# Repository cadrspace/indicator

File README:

# -*- mode: org; -*-

"It's an indicator.  It understands everything, but doesn't speak.  It
only changes colour." -- [[https://en.wikipedia.org/wiki/The_Mystery_of_the_Third_Planet]["The Mystery of the Third Planet"]]

* Requirements
  - [[https://www.gnu.org/software/guile/][GNU Guile]] 2.0+
  - [[https://www.gnu.org/software/guile-rpc/][GNU Guile-RPC]]

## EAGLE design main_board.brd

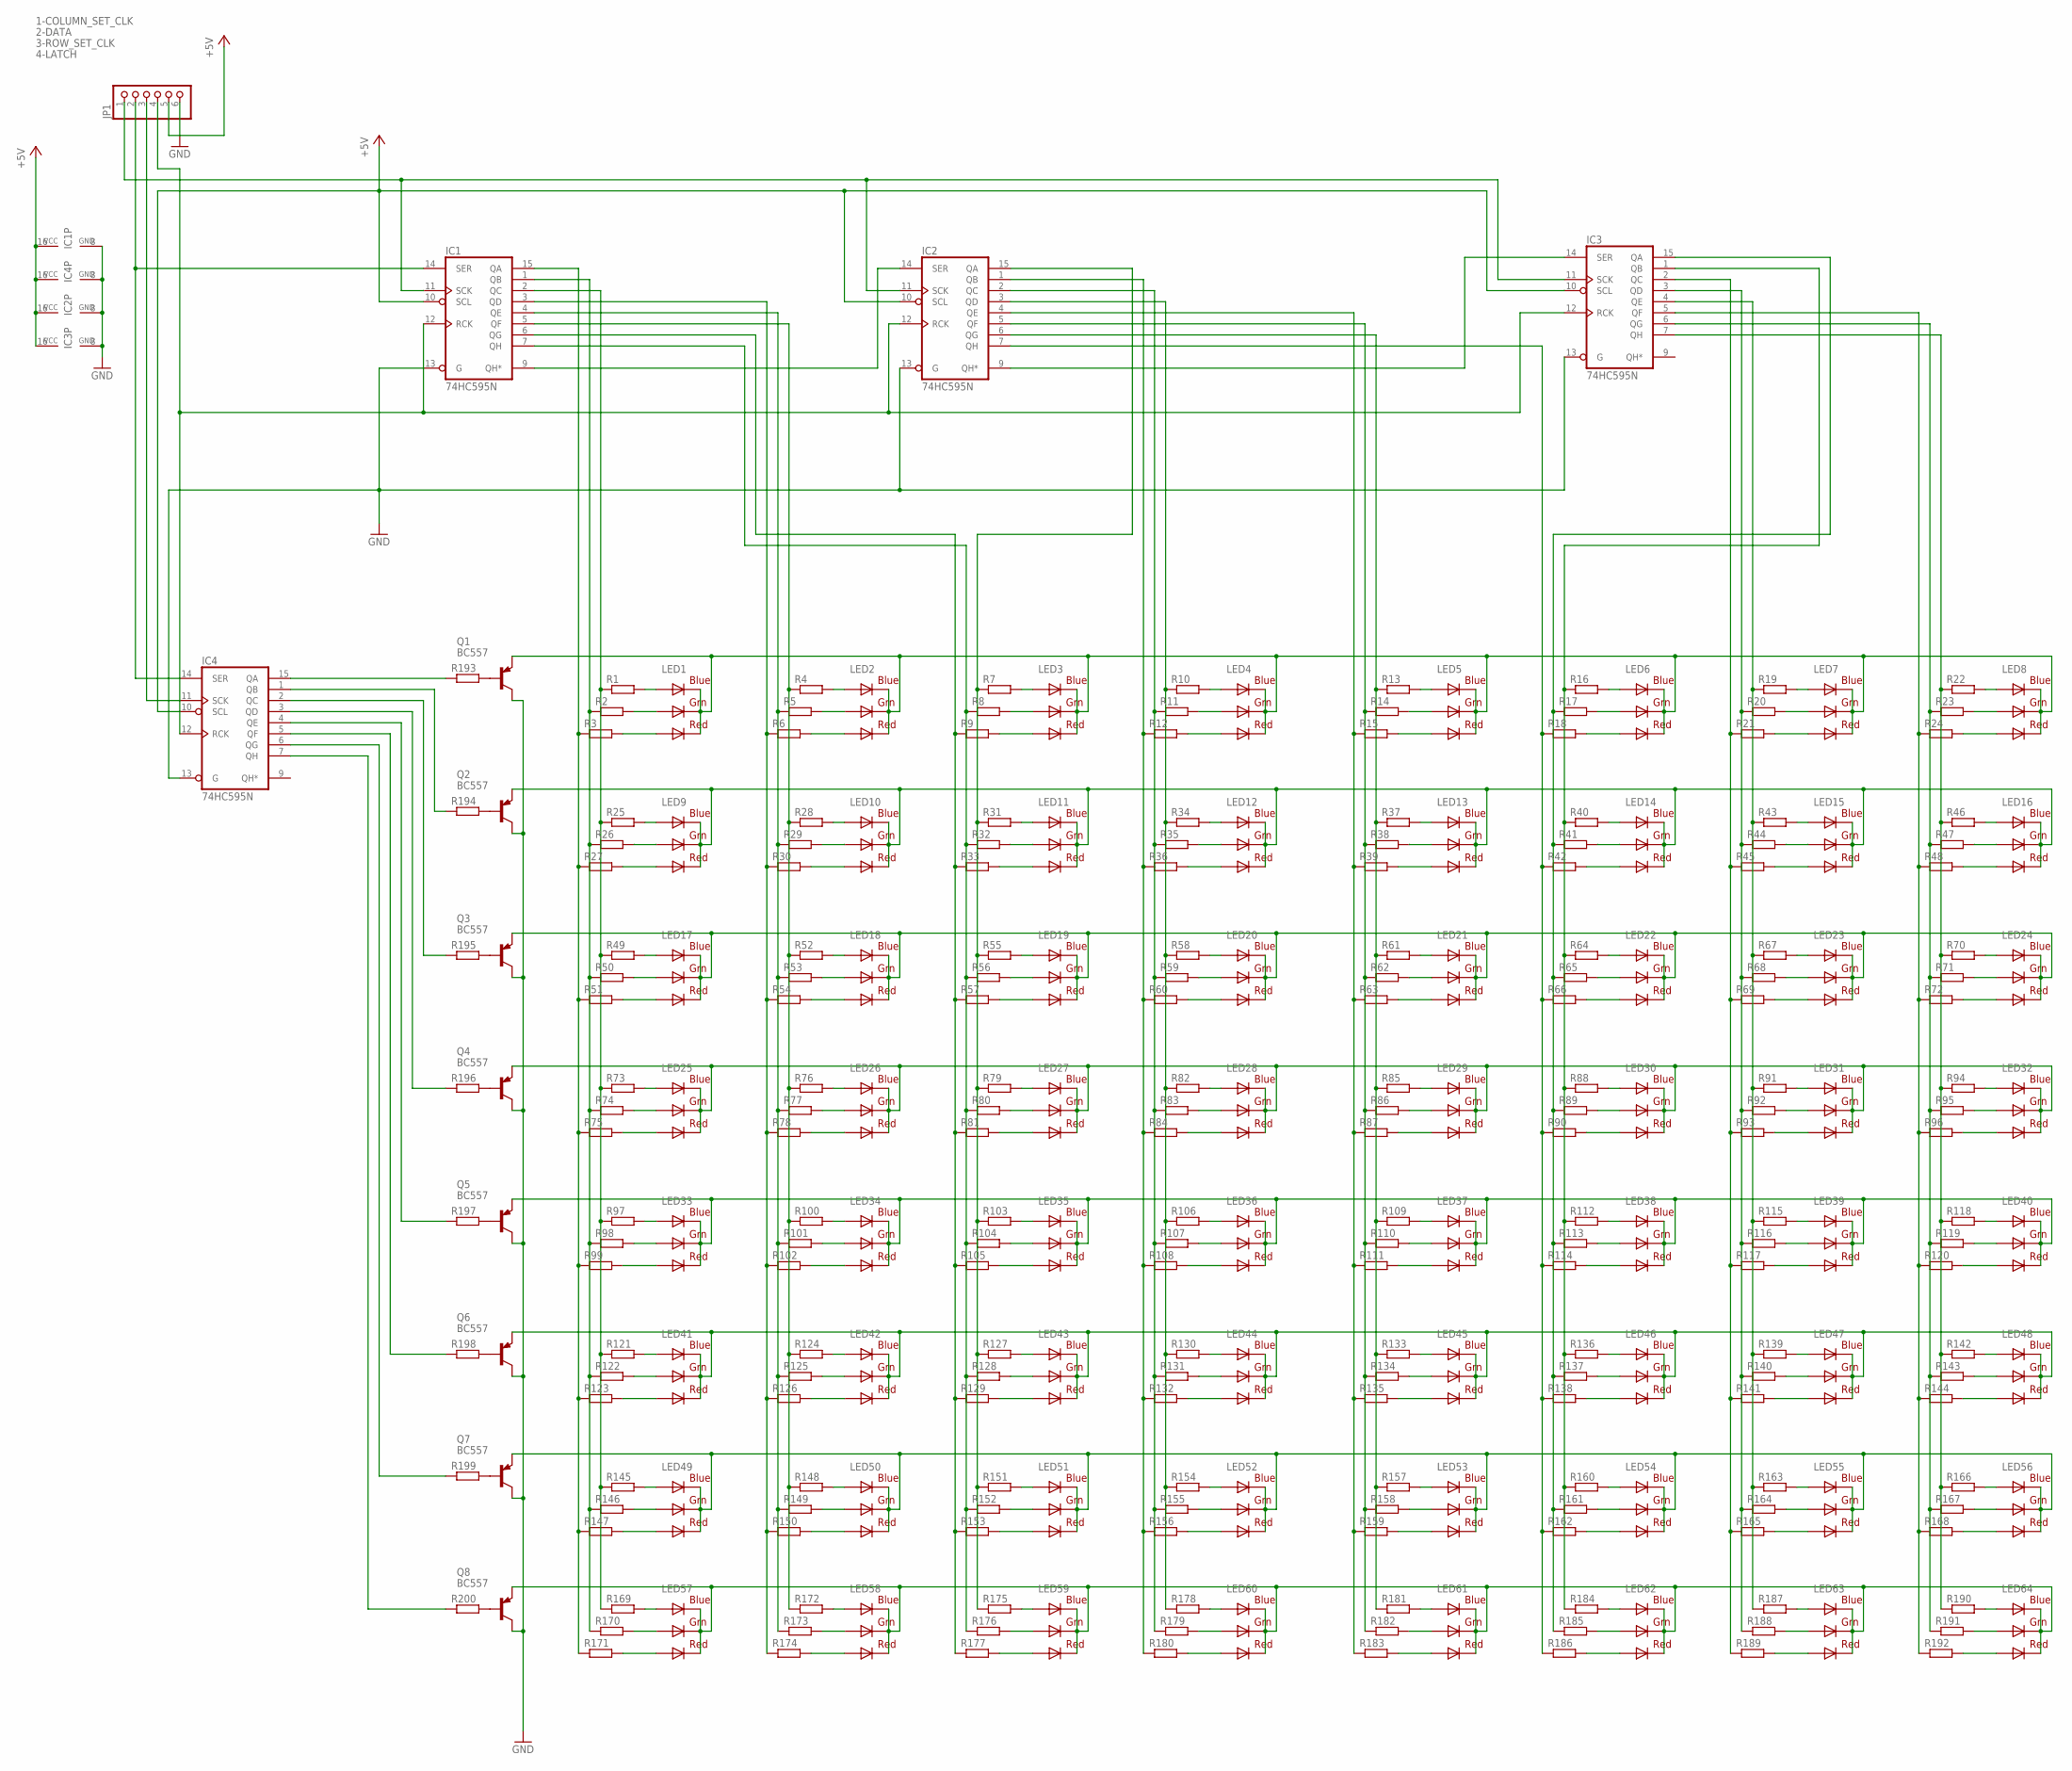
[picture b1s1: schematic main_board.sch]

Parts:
IC1, IC2, IC3, IC4: 74HC595N; DIL16
JP1: PINHD-1X6; 1X06
LED1, LED2, LED3, LED4, LED5, LED6, LED7, LED8, LED9, LED10, LED11, LED12, LED13, LED14, LED15, LED16, LED17, LED18, LED19, LED20, LED21, LED22, LED23, LED24, LED25, LED26, LED27, LED28, LED29, LED30, LED31, LED32, LED33, LED34, LED35, LED36, LED37, LED38, LED39, LED40, LED41, LED42, LED43, LED44, LED45, LED46, LED47, LED48, LED49, LED50, LED51, LED52, LED53, LED54, LED55, LED56, LED57, LED58, LED59, LED60, LED61, LED62, LED63, LED64: RGBLED5050
Q1, Q2, Q3, Q4, Q5, Q6, Q7, Q8: BC557; TO92
R1, R2, R3, R4, R5, R6, R7, R8, R9, R10, R11, R12, R13, R14, R15, R16, R17, R18, R19, R20, R21, R22, R23, R24, R25, R26, R27, R28, R29, R30, R31, R32, R33, R34, R35, R36, R37, R38, R39, R40, R41, R42, R43, R44, R45, R46, R47, R48, R49, R50, R51, R52, R53, R54, R55, R56, R57, R58, R59, R60, R61, R62, R63, R64, R65, R66, R67, R68, R69, R70, R71, R72, R73, R74, R75, R76, R77, R78, R79, R80, R81, R82, R83, R84, R85, R86, R87, R88, R89, R90, R91, R92, R93, R94, R95, R96, R97, R98, R99, R100, R101, R102, R103, R104, R105, R106, R107, R108, R109, R110, R111, R112, R113, R114, R115, R116, R117, R118, R119, R120, R121, R122, R123, R124, R125, R126, R127, R128, R129, R130, R131, R132, R133, R134, R135, R136, R137, R138, R139, R140, R141, R142, R143, R144, R145, R146, R147, R148, R149, R150, R151, R152, R153, R154, R155, R156, R157, R158, R159, R160, R161, R162, R163, R164, R165, R166, R167, R168, R169, R170, R171, R172, R173, R174, R175, R176, R177, R178, R179, R180, R181, R182, R183, R184, R185, R186, R187, R188, R189, R190, R191, R192, R193, R194, R195, R196, R197, R198, R199, R200: R-EU_R0805; R0805

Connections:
1-COLUMN_SET_CLK: IC1.11 (SCK), IC2.11 (SCK), IC3.11 (SCK), JP1.1
2-DATA: IC1.14 (SER), IC4.14 (SER), JP1.2
3-ROW_SET_CLK: IC4.11 (SCK), JP1.3
4-LATCH: IC1.12 (RCK), IC2.12 (RCK), IC3.12 (RCK), IC4.12 (RCK), JP1.4
+5V: IC1.10 (SCL), IC1.16 (VCC), IC2.10 (SCL), IC2.16 (VCC), IC3.10 (SCL), IC3.16 (VCC), IC4.10 (SCL), IC4.16 (VCC), JP1.5
GND: IC1.8 (GND), IC1.13 (G), IC2.8 (GND), IC2.13 (G), IC3.8 (GND), IC3.13 (G), IC4.8 (GND), IC4.13 (G), JP1.6, Q1.3 (C), Q2.3 (C), Q3.3 (C), Q4.3 (C), Q5.3 (C), Q6.3 (C), Q7.3 (C), Q8.3 (C)
unnamed: Q8.2 (B), R200.2
unnamed: LED57.3 (BLUE_A), R169.2
unnamed: LED57.1 (GREEN_A), R170.2
unnamed: LED57.2 (RED_A), R171.2
unnamed: LED58.3 (BLUE_A), R172.2
unnamed: LED58.1 (GREEN_A), R173.2
unnamed: IC2.2 (QC), R11.1, R35.1, R59.1, R83.1, R107.1, R131.1, R155.1, R179.1
unnamed: LED58.2 (RED_A), R174.2
unnamed: LED59.1 (GREEN_A), R176.2
unnamed: LED59.2 (RED_A), R177.2
unnamed: LED59.3 (BLUE_A), R175.2
unnamed: LED1.3 (BLUE_A), R1.2
unnamed: LED1.1 (GREEN_A), R2.2
unnamed: LED1.2 (RED_A), R3.2
unnamed: LED2.3 (BLUE_A), R4.2
unnamed: LED2.1 (GREEN_A), R5.2
unnamed: LED2.2 (RED_A), R6.2
unnamed: LED3.3 (BLUE_A), R7.2
unnamed: LED3.1 (GREEN_A), R8.2
unnamed: LED3.2 (RED_A), R9.2
unnamed: LED4.3 (BLUE_A), R10.2
unnamed: LED4.1 (GREEN_A), R11.2
unnamed: LED4.2 (RED_A), R12.2
unnamed: LED5.3 (BLUE_A), R13.2
unnamed: LED5.1 (GREEN_A), R14.2
unnamed: LED5.2 (RED_A), R15.2
unnamed: LED7.3 (BLUE_A), R19.2
unnamed: LED7.1 (GREEN_A), R20.2
unnamed: LED7.2 (RED_A), R21.2
unnamed: LED8.3 (BLUE_A), R22.2
unnamed: LED8.1 (GREEN_A), R23.2
unnamed: LED8.2 (RED_A), R24.2
unnamed: LED9.3 (BLUE_A), R25.2
unnamed: LED9.1 (GREEN_A), R26.2
unnamed: LED9.2 (RED_A), R27.2
unnamed: LED10.3 (BLUE_A), R28.2
unnamed: LED10.1 (GREEN_A), R29.2
unnamed: LED10.2 (RED_A), R30.2
unnamed: LED11.3 (BLUE_A), R31.2
unnamed: LED11.1 (GREEN_A), R32.2
unnamed: LED11.2 (RED_A), R33.2
unnamed: LED12.3 (BLUE_A), R34.2
unnamed: LED12.1 (GREEN_A), R35.2
unnamed: LED12.2 (RED_A), R36.2
unnamed: LED13.3 (BLUE_A), R37.2
unnamed: LED13.1 (GREEN_A), R38.2
unnamed: LED13.2 (RED_A), R39.2
unnamed: LED6.3 (BLUE_A), R16.2
unnamed: LED6.1 (GREEN_A), R17.2
unnamed: LED6.2 (RED_A), R18.2
unnamed: LED14.3 (BLUE_A), R40.2
unnamed: LED14.1 (GREEN_A), R41.2
unnamed: LED14.2 (RED_A), R42.2
unnamed: LED17.3 (BLUE_A), R49.2
unnamed: LED17.1 (GREEN_A), R50.2
unnamed: LED17.2 (RED_A), R51.2
unnamed: LED15.3 (BLUE_A), R43.2
unnamed: LED15.1 (GREEN_A), R44.2
unnamed: LED15.2 (RED_A), R45.2
unnamed: LED16.3 (BLUE_A), R46.2
unnamed: LED16.1 (GREEN_A), R47.2
unnamed: LED16.2 (RED_A), R48.2
unnamed: LED18.3 (BLUE_A), R52.2
unnamed: LED18.1 (GREEN_A), R53.2
unnamed: LED18.2 (RED_A), R54.2
unnamed: LED19.3 (BLUE_A), R55.2
unnamed: LED19.1 (GREEN_A), R56.2
unnamed: LED19.2 (RED_A), R57.2
unnamed: LED20.3 (BLUE_A), R58.2
unnamed: LED20.1 (GREEN_A), R59.2
unnamed: LED20.2 (RED_A), R60.2
unnamed: LED21.3 (BLUE_A), R61.2
unnamed: LED21.1 (GREEN_A), R62.2
unnamed: LED21.2 (RED_A), R63.2
unnamed: LED22.3 (BLUE_A), R64.2
unnamed: LED22.1 (GREEN_A), R65.2
unnamed: LED22.2 (RED_A), R66.2
unnamed: LED23.3 (BLUE_A), R67.2
unnamed: LED23.1 (GREEN_A), R68.2
unnamed: LED23.2 (RED_A), R69.2
unnamed: LED24.3 (BLUE_A), R70.2
unnamed: LED24.1 (GREEN_A), R71.2
unnamed: LED24.2 (RED_A), R72.2
unnamed: LED25.3 (BLUE_A), R73.2
unnamed: LED25.1 (GREEN_A), R74.2
unnamed: LED25.2 (RED_A), R75.2
unnamed: LED26.3 (BLUE_A), R76.2
unnamed: LED26.1 (GREEN_A), R77.2
unnamed: LED26.2 (RED_A), R78.2
unnamed: LED27.3 (BLUE_A), R79.2
unnamed: LED27.1 (GREEN_A), R80.2
unnamed: LED27.2 (RED_A), R81.2
unnamed: LED28.3 (BLUE_A), R82.2
unnamed: LED28.1 (GREEN_A), R83.2
unnamed: LED28.2 (RED_A), R84.2
unnamed: LED29.3 (BLUE_A), R85.2
unnamed: LED29.1 (GREEN_A), R86.2
unnamed: LED29.2 (RED_A), R87.2
unnamed: LED30.3 (BLUE_A), R88.2
unnamed: LED30.1 (GREEN_A), R89.2
unnamed: LED30.2 (RED_A), R90.2
unnamed: LED31.2 (RED_A), R93.2
unnamed: LED31.1 (GREEN_A), R92.2
unnamed: LED31.3 (BLUE_A), R91.2
unnamed: LED32.2 (RED_A), R96.2
unnamed: LED32.1 (GREEN_A), R95.2
unnamed: LED32.3 (BLUE_A), R94.2
unnamed: LED33.3 (BLUE_A), R97.2
unnamed: LED33.1 (GREEN_A), R98.2
unnamed: LED33.2 (RED_A), R99.2
unnamed: LED34.3 (BLUE_A), R100.2
unnamed: LED34.1 (GREEN_A), R101.2
unnamed: LED34.2 (RED_A), R102.2
unnamed: LED35.3 (BLUE_A), R103.2
unnamed: LED35.1 (GREEN_A), R104.2
unnamed: LED35.2 (RED_A), R105.2
unnamed: LED36.3 (BLUE_A), R106.2
unnamed: LED36.1 (GREEN_A), R107.2
unnamed: LED36.2 (RED_A), R108.2
unnamed: LED37.3 (BLUE_A), R109.2
unnamed: LED37.1 (GREEN_A), R110.2
unnamed: LED37.2 (RED_A), R111.2
unnamed: LED38.3 (BLUE_A), R112.2
unnamed: LED38.1 (GREEN_A), R113.2
unnamed: LED38.2 (RED_A), R114.2
unnamed: LED39.3 (BLUE_A), R115.2
unnamed: LED39.1 (GREEN_A), R116.2
unnamed: LED39.2 (RED_A), R117.2
unnamed: LED40.3 (BLUE_A), R118.2
unnamed: LED40.1 (GREEN_A), R119.2
unnamed: LED40.2 (RED_A), R120.2
unnamed: LED41.3 (BLUE_A), R121.2
unnamed: LED41.1 (GREEN_A), R122.2
unnamed: LED41.2 (RED_A), R123.2
unnamed: LED42.3 (BLUE_A), R124.2
unnamed: LED42.1 (GREEN_A), R125.2
unnamed: LED42.2 (RED_A), R126.2
unnamed: LED43.3 (BLUE_A), R127.2
unnamed: LED43.1 (GREEN_A), R128.2
unnamed: LED43.2 (RED_A), R129.2
unnamed: LED44.3 (BLUE_A), R130.2
unnamed: LED44.1 (GREEN_A), R131.2
unnamed: LED44.2 (RED_A), R132.2
unnamed: LED45.3 (BLUE_A), R133.2
unnamed: LED45.1 (GREEN_A), R134.2
unnamed: LED45.2 (RED_A), R135.2
unnamed: LED46.3 (BLUE_A), R136.2
unnamed: LED46.1 (GREEN_A), R137.2
unnamed: LED46.2 (RED_A), R138.2
unnamed: LED47.3 (BLUE_A), R139.2
unnamed: LED47.1 (GREEN_A), R140.2
unnamed: LED47.2 (RED_A), R141.2
unnamed: LED48.3 (BLUE_A), R142.2
unnamed: LED48.1 (GREEN_A), R143.2
unnamed: LED48.2 (RED_A), R144.2
unnamed: LED49.3 (BLUE_A), R145.2
unnamed: LED49.1 (GREEN_A), R146.2
unnamed: LED49.2 (RED_A), R147.2
unnamed: LED50.3 (BLUE_A), R148.2
unnamed: LED50.1 (GREEN_A), R149.2
unnamed: LED50.2 (RED_A), R150.2
unnamed: LED51.3 (BLUE_A), R151.2
unnamed: LED51.1 (GREEN_A), R152.2
unnamed: LED51.2 (RED_A), R153.2
unnamed: LED52.3 (BLUE_A), R154.2
unnamed: LED52.1 (GREEN_A), R155.2
unnamed: LED52.2 (RED_A), R156.2
unnamed: LED53.3 (BLUE_A), R157.2
unnamed: LED53.1 (GREEN_A), R158.2
unnamed: LED53.2 (RED_A), R159.2
unnamed: LED54.3 (BLUE_A), R160.2
unnamed: LED54.1 (GREEN_A), R161.2
unnamed: LED54.2 (RED_A), R162.2
unnamed: LED55.3 (BLUE_A), R163.2
unnamed: LED55.1 (GREEN_A), R164.2
unnamed: LED55.2 (RED_A), R165.2
unnamed: LED56.3 (BLUE_A), R166.2
unnamed: LED56.1 (GREEN_A), R167.2
unnamed: LED56.2 (RED_A), R168.2
unnamed: LED60.3 (BLUE_A), R178.2
unnamed: LED60.1 (GREEN_A), R179.2
unnamed: LED60.2 (RED_A), R180.2
unnamed: LED61.3 (BLUE_A), R181.2
unnamed: LED61.1 (GREEN_A), R182.2
unnamed: LED61.2 (RED_A), R183.2
unnamed: LED62.3 (BLUE_A), R184.2
unnamed: LED62.1 (GREEN_A), R185.2
unnamed: LED62.2 (RED_A), R186.2
unnamed: LED63.3 (BLUE_A), R187.2
unnamed: LED63.1 (GREEN_A), R188.2
unnamed: LED63.2 (RED_A), R189.2
unnamed: LED64.3 (BLUE_A), R190.2
unnamed: LED64.1 (GREEN_A), R191.2
unnamed: LED64.2 (RED_A), R192.2
unnamed: LED1.4 (BLUE_C), LED1.5 (RED_C), LED1.6 (GREEN_C), LED2.4 (BLUE_C), LED2.5 (RED_C), LED2.6 (GREEN_C), LED3.4 (BLUE_C), LED3.5 (RED_C), LED3.6 (GREEN_C), LED4.4 (BLUE_C), LED4.5 (RED_C), LED4.6 (GREEN_C), LED5.4 (BLUE_C), LED5.5 (RED_C), LED5.6 (GREEN_C), LED6.4 (BLUE_C), LED6.5 (RED_C), LED6.6 (GREEN_C), LED7.4 (BLUE_C), LED7.5 (RED_C), LED7.6 (GREEN_C), LED8.4 (BLUE_C), LED8.5 (RED_C), LED8.6 (GREEN_C), Q1.1 (E)
unnamed: LED17.4 (BLUE_C), LED17.5 (RED_C), LED17.6 (GREEN_C), LED18.4 (BLUE_C), LED18.5 (RED_C), LED18.6 (GREEN_C), LED19.4 (BLUE_C), LED19.5 (RED_C), LED19.6 (GREEN_C), LED20.4 (BLUE_C), LED20.5 (RED_C), LED20.6 (GREEN_C), LED21.4 (BLUE_C), LED21.5 (RED_C), LED21.6 (GREEN_C), LED22.4 (BLUE_C), LED22.5 (RED_C), LED22.6 (GREEN_C), LED23.4 (BLUE_C), LED23.5 (RED_C), LED23.6 (GREEN_C), LED24.4 (BLUE_C), LED24.5 (RED_C), LED24.6 (GREEN_C), Q3.1 (E)
unnamed: Q2.2 (B), R194.2
unnamed: LED9.4 (BLUE_C), LED9.5 (RED_C), LED9.6 (GREEN_C), LED10.4 (BLUE_C), LED10.5 (RED_C), LED10.6 (GREEN_C), LED11.4 (BLUE_C), LED11.5 (RED_C), LED11.6 (GREEN_C), LED12.4 (BLUE_C), LED12.5 (RED_C), LED12.6 (GREEN_C), LED13.4 (BLUE_C), LED13.5 (RED_C), LED13.6 (GREEN_C), LED14.4 (BLUE_C), LED14.5 (RED_C), LED14.6 (GREEN_C), LED15.4 (BLUE_C), LED15.5 (RED_C), LED15.6 (GREEN_C), LED16.4 (BLUE_C), LED16.5 (RED_C), LED16.6 (GREEN_C), Q2.1 (E)
unnamed: IC4.4 (QE), R197.1
unnamed: LED41.4 (BLUE_C), LED41.5 (RED_C), LED41.6 (GREEN_C), LED42.4 (BLUE_C), LED42.5 (RED_C), LED42.6 (GREEN_C), LED43.4 (BLUE_C), LED43.5 (RED_C), LED43.6 (GREEN_C), LED44.4 (BLUE_C), LED44.5 (RED_C), LED44.6 (GREEN_C), LED45.4 (BLUE_C), LED45.5 (RED_C), LED45.6 (GREEN_C), LED46.4 (BLUE_C), LED46.5 (RED_C), LED46.6 (GREEN_C), LED47.4 (BLUE_C), LED47.5 (RED_C), LED47.6 (GREEN_C), LED48.4 (BLUE_C), LED48.5 (RED_C), LED48.6 (GREEN_C), Q6.1 (E)
unnamed: IC4.6 (QG), R199.1
unnamed: IC4.7 (QH), R200.1
unnamed: IC4.2 (QC), R195.1
unnamed: LED25.4 (BLUE_C), LED25.5 (RED_C), LED25.6 (GREEN_C), LED26.4 (BLUE_C), LED26.5 (RED_C), LED26.6 (GREEN_C), LED27.4 (BLUE_C), LED27.5 (RED_C), LED27.6 (GREEN_C), LED28.4 (BLUE_C), LED28.5 (RED_C), LED28.6 (GREEN_C), LED29.4 (BLUE_C), LED29.5 (RED_C), LED29.6 (GREEN_C), LED30.4 (BLUE_C), LED30.5 (RED_C), LED30.6 (GREEN_C), LED31.4 (BLUE_C), LED31.5 (RED_C), LED31.6 (GREEN_C), LED32.4 (BLUE_C), LED32.5 (RED_C), LED32.6 (GREEN_C), Q4.1 (E)
unnamed: IC1.15 (QA), R3.1, R27.1, R51.1, R75.1, R99.1, R123.1, R147.1, R171.1
unnamed: IC4.1 (QB), R194.1
unnamed: IC4.3 (QD), R196.1
unnamed: LED33.4 (BLUE_C), LED33.5 (RED_C), LED33.6 (GREEN_C), LED34.4 (BLUE_C), LED34.5 (RED_C), LED34.6 (GREEN_C), LED35.4 (BLUE_C), LED35.5 (RED_C), LED35.6 (GREEN_C), LED36.4 (BLUE_C), LED36.5 (RED_C), LED36.6 (GREEN_C), LED37.4 (BLUE_C), LED37.5 (RED_C), LED37.6 (GREEN_C), LED38.4 (BLUE_C), LED38.5 (RED_C), LED38.6 (GREEN_C), LED39.4 (BLUE_C), LED39.5 (RED_C), LED39.6 (GREEN_C), LED40.4 (BLUE_C), LED40.5 (RED_C), LED40.6 (GREEN_C), Q5.1 (E)
unnamed: IC1.1 (QB), R2.1, R26.1, R50.1, R74.1, R98.1, R122.1, R146.1, R170.1
unnamed: IC1.2 (QC), R1.1, R25.1, R49.1, R73.1, R97.1, R121.1, R145.1, R169.1
unnamed: IC1.3 (QD), R6.1, R30.1, R54.1, R78.1, R102.1, R126.1, R150.1, R174.1
unnamed: LED57.4 (BLUE_C), LED57.5 (RED_C), LED57.6 (GREEN_C), LED58.4 (BLUE_C), LED58.5 (RED_C), LED58.6 (GREEN_C), LED59.4 (BLUE_C), LED59.5 (RED_C), LED59.6 (GREEN_C), LED60.4 (BLUE_C), LED60.5 (RED_C), LED60.6 (GREEN_C), LED61.4 (BLUE_C), LED61.5 (RED_C), LED61.6 (GREEN_C), LED62.4 (BLUE_C), LED62.5 (RED_C), LED62.6 (GREEN_C), LED63.4 (BLUE_C), LED63.5 (RED_C), LED63.6 (GREEN_C), LED64.4 (BLUE_C), LED64.5 (RED_C), LED64.6 (GREEN_C), Q8.1 (E)
unnamed: IC4.5 (QF), R198.1
unnamed: LED49.4 (BLUE_C), LED49.5 (RED_C), LED49.6 (GREEN_C), LED50.4 (BLUE_C), LED50.5 (RED_C), LED50.6 (GREEN_C), LED51.4 (BLUE_C), LED51.5 (RED_C), LED51.6 (GREEN_C), LED52.4 (BLUE_C), LED52.5 (RED_C), LED52.6 (GREEN_C), LED53.4 (BLUE_C), LED53.5 (RED_C), LED53.6 (GREEN_C), LED54.4 (BLUE_C), LED54.5 (RED_C), LED54.6 (GREEN_C), LED55.4 (BLUE_C), LED55.5 (RED_C), LED55.6 (GREEN_C), LED56.4 (BLUE_C), LED56.5 (RED_C), LED56.6 (GREEN_C), Q7.1 (E)
unnamed: IC1.4 (QE), R5.1, R29.1, R53.1, R77.1, R101.1, R125.1, R149.1, R173.1
unnamed: IC1.5 (QF), R4.1, R28.1, R52.1, R76.1, R100.1, R124.1, R148.1, R172.1
unnamed: IC1.6 (QG), R9.1, R33.1, R57.1, R81.1, R105.1, R129.1, R153.1, R177.1
unnamed: IC1.7 (QH), R8.1, R32.1, R56.1, R80.1, R104.1, R128.1, R152.1, R176.1
unnamed: IC2.15 (QA), R7.1, R31.1, R55.1, R79.1, R103.1, R127.1, R151.1, R175.1
unnamed: IC2.7 (QH), R18.1, R42.1, R66.1, R90.1, R114.1, R138.1, R162.1, R186.1
unnamed: IC2.3 (QD), R10.1, R34.1, R58.1, R82.1, R106.1, R130.1, R154.1, R178.1
unnamed: IC2.1 (QB), R12.1, R36.1, R60.1, R84.1, R108.1, R132.1, R156.1, R180.1
unnamed: IC2.4 (QE), R15.1, R39.1, R63.1, R87.1, R111.1, R135.1, R159.1, R183.1
unnamed: IC2.5 (QF), R14.1, R38.1, R62.1, R86.1, R110.1, R134.1, R158.1, R182.1
unnamed: IC2.6 (QG), R13.1, R37.1, R61.1, R85.1, R109.1, R133.1, R157.1, R181.1
unnamed: IC3.15 (QA), R17.1, R41.1, R65.1, R89.1, R113.1, R137.1, R161.1, R185.1
unnamed: IC3.1 (QB), R16.1, R40.1, R64.1, R88.1, R112.1, R136.1, R160.1, R184.1
unnamed: IC3.2 (QC), R21.1, R45.1, R69.1, R93.1, R117.1, R141.1, R165.1, R189.1
unnamed: IC3.3 (QD), R20.1, R44.1, R68.1, R92.1, R116.1, R140.1, R164.1, R188.1
unnamed: IC3.4 (QE), R19.1, R43.1, R67.1, R91.1, R115.1, R139.1, R163.1, R187.1
unnamed: IC3.5 (QF), R24.1, R48.1, R72.1, R96.1, R120.1, R144.1, R168.1, R192.1
unnamed: IC3.6 (QG), R23.1, R47.1, R71.1, R95.1, R119.1, R143.1, R167.1, R191.1
unnamed: IC3.7 (QH), R22.1, R46.1, R70.1, R94.1, R118.1, R142.1, R166.1, R190.1
unnamed: IC2.9 (QH*), IC3.14 (SER)
unnamed: Q3.2 (B), R195.2
unnamed: IC1.9 (QH*), IC2.14 (SER)
unnamed: Q4.2 (B), R196.2
unnamed: Q5.2 (B), R197.2
unnamed: Q6.2 (B), R198.2
unnamed: Q7.2 (B), R199.2
unnamed: IC4.15 (QA), R193.1
unnamed: Q1.2 (B), R193.2

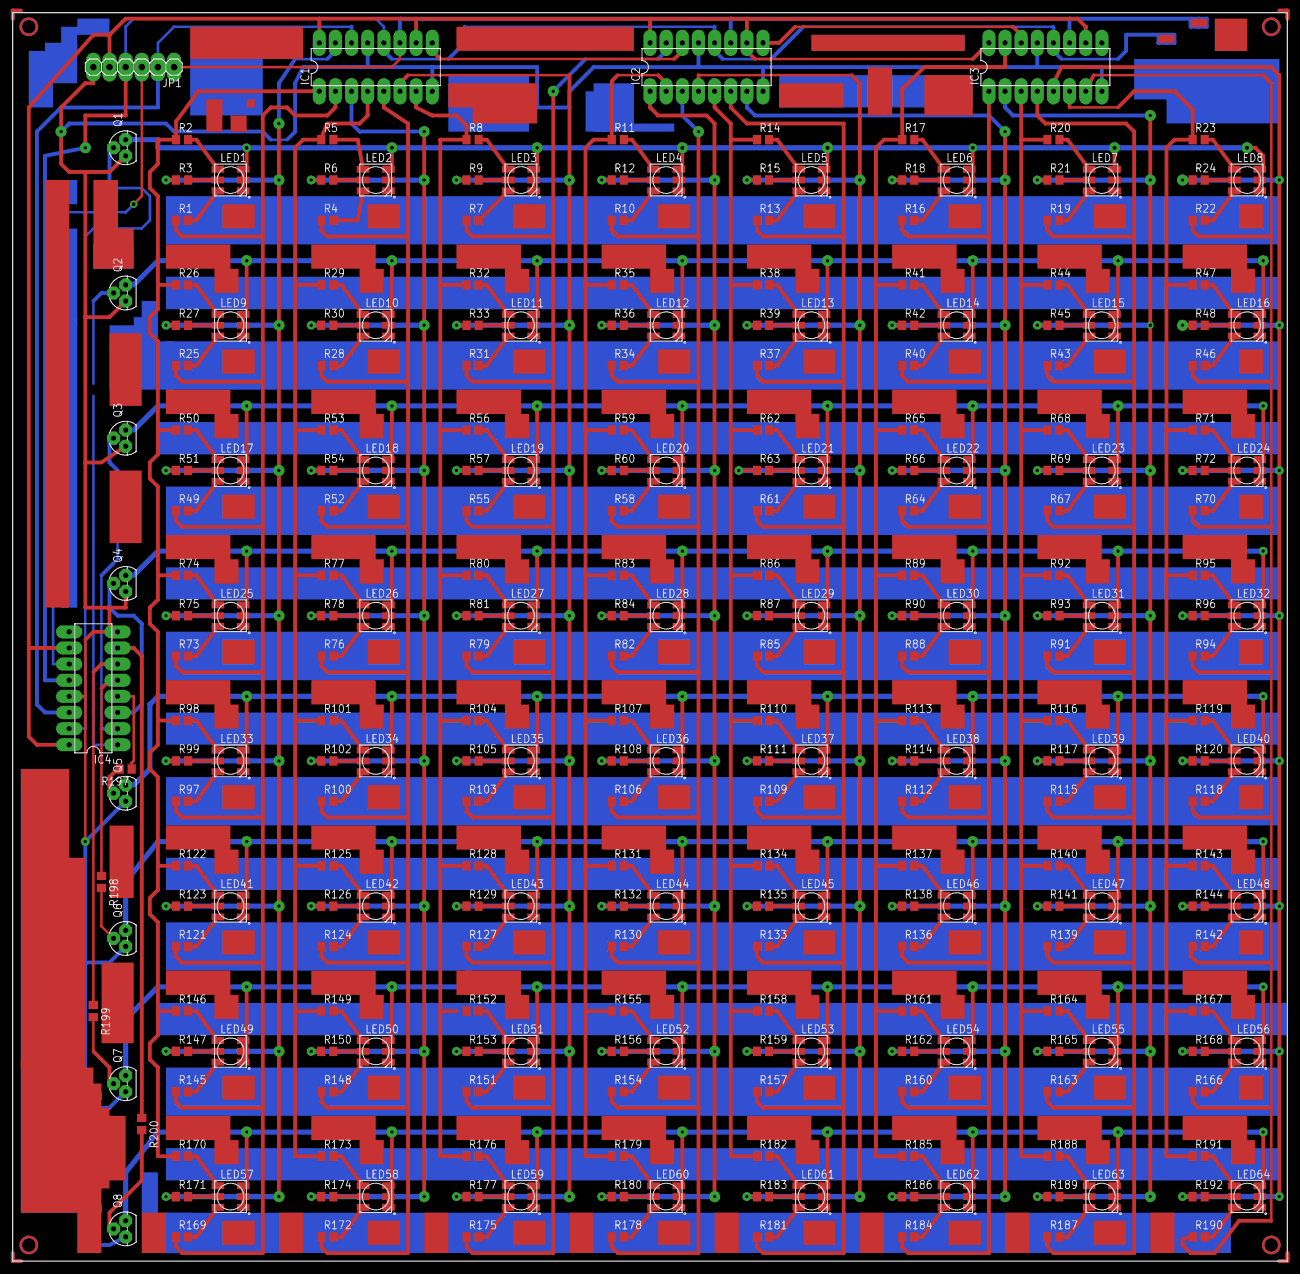
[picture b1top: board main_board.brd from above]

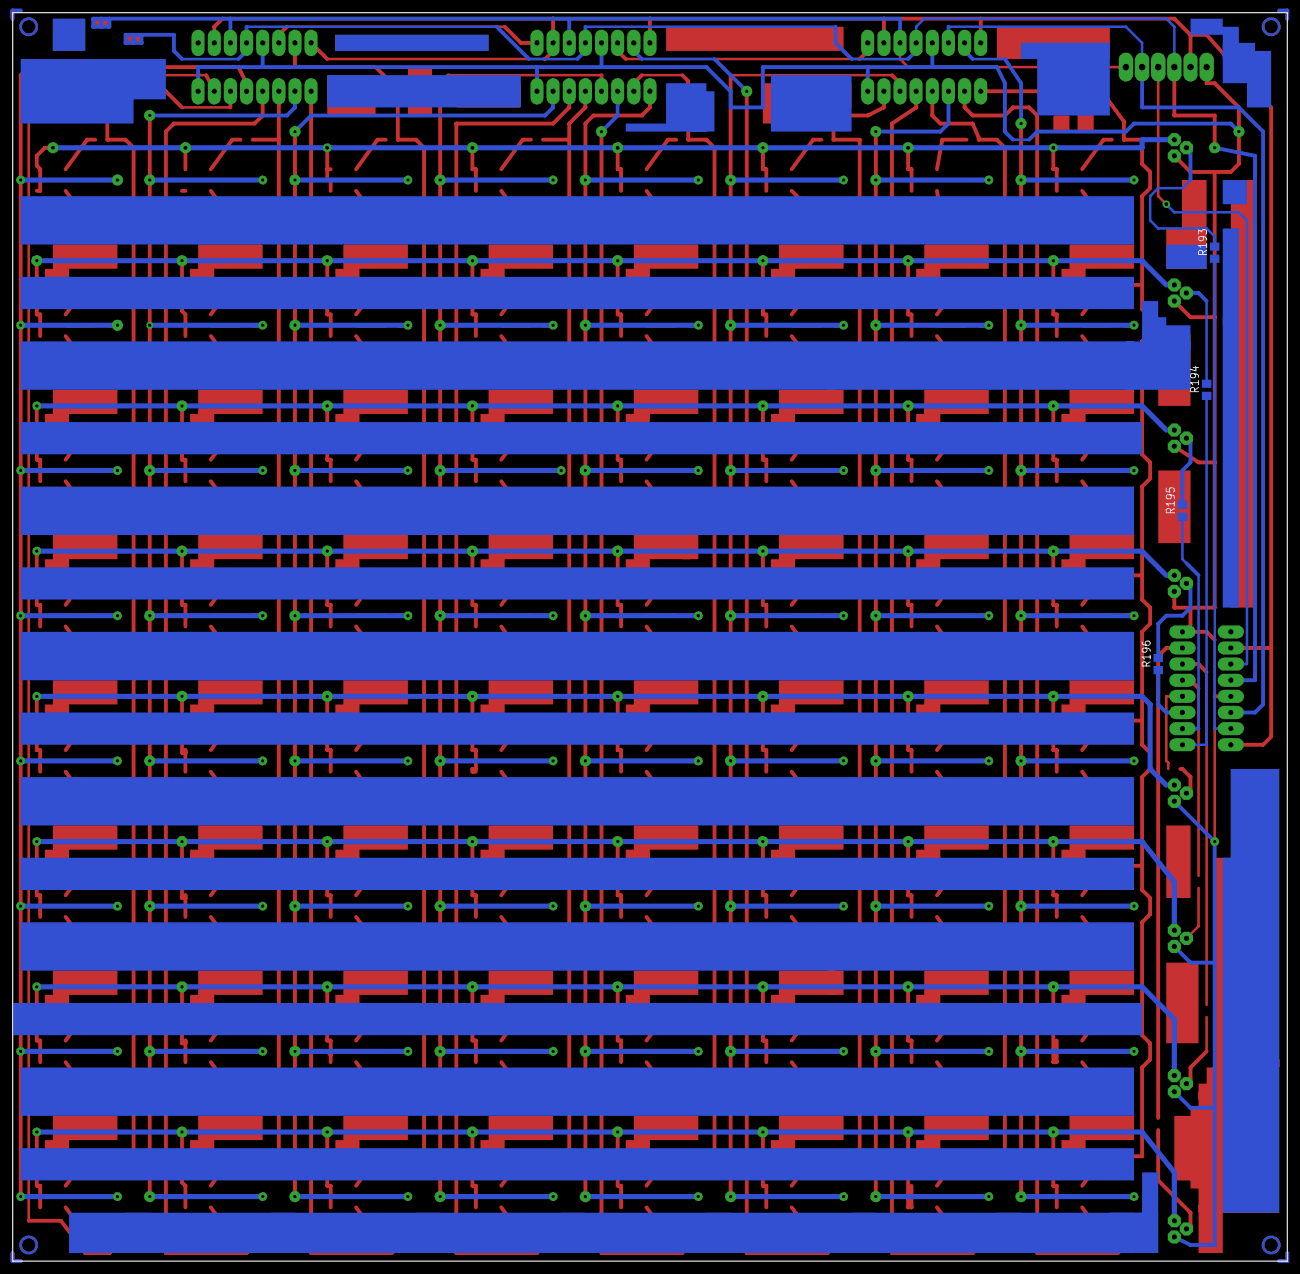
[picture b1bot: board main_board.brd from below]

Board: 2 copper layers, 200.6 x 196.5 mm, 277 parts (4 on the bottom side), 248 nets.

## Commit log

2014-07-07 indicator.ino (state_test): New state
    * indicator.ino (state_test): New state.
    (loop): Add it.
    (shiftOut, state_heartbeat): Use short values.
2014-07-22 Update indicator.ino
    add led demo functionality
2014-07-31 indicator.ino: Fix coding style
2014-07-31 indicator.ino: Rename to `ino/indicator.ino'
2014-08-01 Add termios Guile module. Add GNU Autotools files.
    * termios/: Add to the repository.
    * Makefile.am, configure.ac: Likewise.
    * am/Makefile.am, am/guilec, am/snarf: Likewise.
    * build-aux/Makefile.am: Likewise.
    * m4/guile.m4, m4/lib-link.m4: Likewise.
    * AUTHORS, COPYING, ChangeLog, INSTALL, NEWS, README: Likewise.
2014-08-01 configure.ac (AC_CONFIG_FILES): Add missing Makefile
2014-08-01 configure.ac (LIBGUILE_TERMIOS_INTERFACE): Fix the current version
2014-08-01 ino/indicator.ino (set_led): Fix a bug
2014-08-02 termios/.gitignore: Add to the repository
2014-08-02 .gitignore: Ignore some auxiliary files and dirs
2014-08-02 ino/indicator.ino (state_test): Remove.
    * ino/indicator.ino (state_test): Remove.
    (led_demo): Rename to `state_demo'.
    (loop): Add it.
2014-08-07 termios.scm (tcsetattr): Rename to `tcsetattr!'
    * termios.scm (tcsetattr): Rename to `tcsetattr!'
    * termios-func.c (gtermios_tcsetattr_x): Change Scheme name to
    `%tcsetattr!'.
2014-08-07 termios.scm (cfmakeraw!): New procedure
    * termios.scm (cfmakeraw!): New procedure
    * termios-func.c (gtermios_cfmakeraw_x): Likewise.
2014-08-07 ino/indicator.ino (state_heartbeat): Improve
    * ino/indicator.ino (state_heartbeat): Use `set_led'. Use the central
    diode to indicate heartbeats.
2014-08-08 ino: Rename to `indicator'
2014-08-10 indicator/indicator.in: Add RPC server stub
    * indicator/indicator.in, indicator/rpc.x: Add to the repository.
    * Makefile.am (SUBDIRS): Add `indicator' directory.
    * configure.ac (AC_CONFIG_FILES): Add `indicator/Makefile'.
    * indicator/.gitignore: Ignore generated files.
    * indicator/Makefile.am: Add to the repository.
2014-08-10 README (Requirements): New section
    * README (Requirements): New section
    * README.org: Symlink to README
2014-08-10 indicator.in (main): Open serial port
    * indicator.in (main): Add `--device' option. Open a serial port.
    (set-status): Actually set Indicator status.
    (open-and-configure-device): New procedure.
    (print-help-and-exit): Update.
2014-08-10 rpc.x: Rename `set_status' to set_state
    * rpc.x: Rename `set_status' to set_state.
    * indicator.in (set-status): Rename to `set-state'. All callers
    updated.
    (run-rpc-server): Update.
2014-08-10 indicator.in (set-state): Make it work
    * indicator/indicator.in (open-and-configure-device): Set `O_NONBLOCK'
    and `O_NDELAY' options for the port.
    (set-state): Open the port every time the procedure called, close it
    at the end.
    (open-server-socket): Reuse the address.
    (main): Store the path to the serial port device.
2014-08-10 indicator/indicator.in: Add copyright notice
2014-08-10 README: Update
2015-10-23 modules: Add to the repository
2016-06-10 Add files via upload
    LED board schematic
2016-06-14 Add files via upload
    Main board layout
2019-02-04 replaced to add new architect implemetation
2019-02-04 Indicator library implementation
    Library implementation is more usefull method to develop Indicator's apps.
